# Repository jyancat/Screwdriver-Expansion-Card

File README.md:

# Screwdriver Expansion Card
 This is the GitHub repository for the files to make the screwdriver expansion card with a passthrough port and screwdriver slot and storage.

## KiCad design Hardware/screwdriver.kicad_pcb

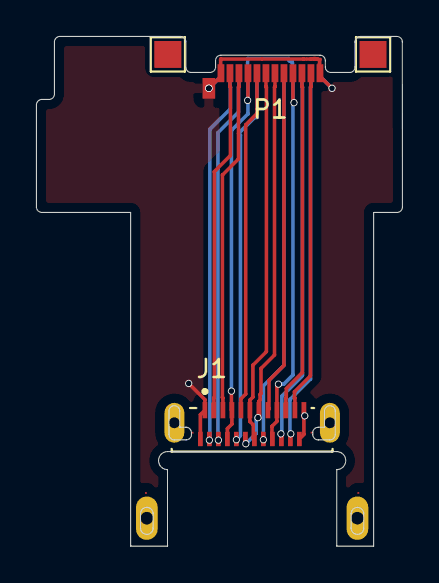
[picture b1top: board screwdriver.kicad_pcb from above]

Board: 2 copper layers, 20.3 x 28.3 mm, 4 parts (0 on the bottom side), 16 nets.

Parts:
J1: USB_C_Receptacle; JAE_DX07B024JJ1R1500
P1: USB_C_Plug; USB_C_Plug_Molex_105444
TP1, TP3: TestPoint; TestPoint_Pad_1.5x1.5mm

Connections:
CC: J1.A5, P1.A5
D+: J1.A6, J1.B6, P1.A6
D-: J1.A7, J1.B7, P1.A7
GND: J1.A1, J1.A12, J1.B1, J1.B12, P1.A1, P1.A12, P1.B1, P1.B12, P1.S1
RX1+: J1.B11, P1.B11
RX1-: J1.B10, P1.B10
RX2+: J1.A11, P1.A11
RX2-: J1.A10, P1.A10
SBU1: J1.A8, P1.A8
SBU2: J1.B8, P1.B8
TX1+: J1.A2, P1.A2
TX1-: J1.A3, P1.A3
TX2+: J1.B2, P1.B2
TX2-: J1.B3, P1.B3
VBUS: J1.A4, J1.A9, J1.B4, J1.B9, P1.A4, P1.A9, P1.B4, P1.B9
VCONN: J1.B5, P1.B5

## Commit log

2022-05-18 Committed Files.
